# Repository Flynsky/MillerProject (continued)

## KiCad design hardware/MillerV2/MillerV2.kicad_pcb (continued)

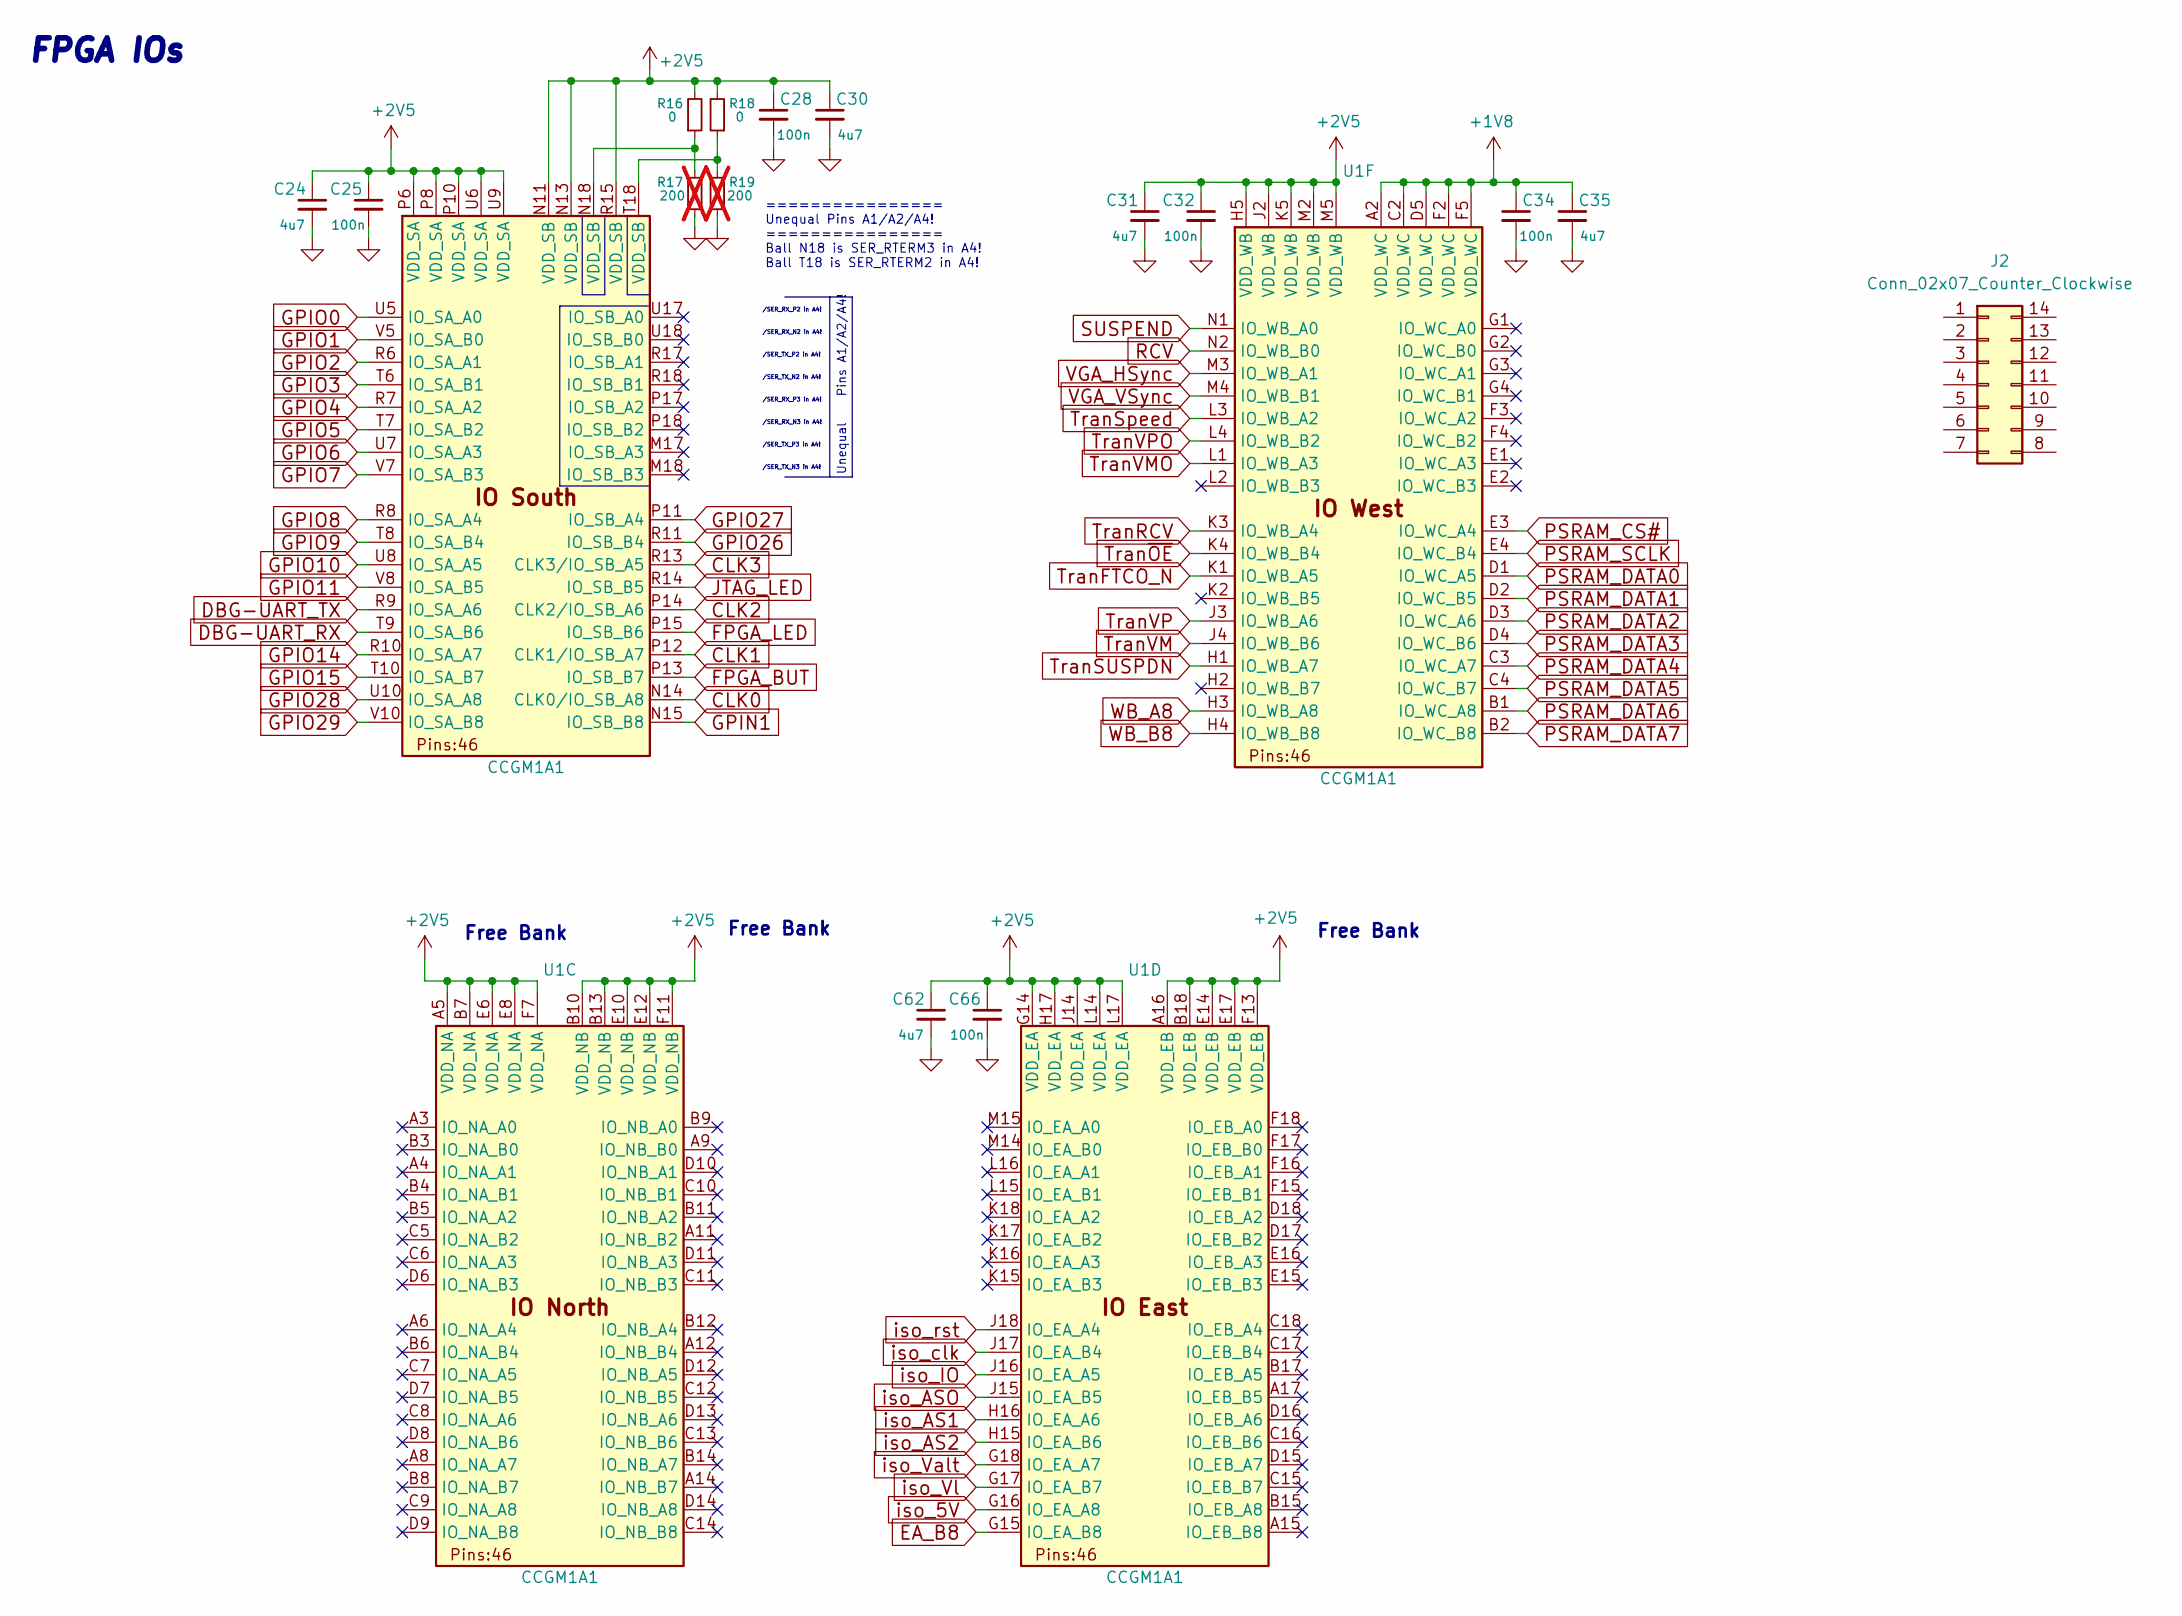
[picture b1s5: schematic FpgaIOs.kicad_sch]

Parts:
C24, C30, C31, C35, C62: 4u7; C_0402_1005Metric
C25, C28, C32, C34, C66: 100n; C_0402_1005Metric
J2: Conn_02x07_Counter_Clockwise; PinSocket_2x07_P2.54mm_Vertical_SMD
R16, R18: 0; R_0402_1005Metric
R17, R19: 200; R_0402_1005Metric; not fitted
U1: CCGM1A1; BGA-324_15x15mm_Layout18x18_P0.8mm_improvedUrsprung

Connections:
+1V8: C34.1, C35.1, U1.A2 (VDD_WC), U1.C2 (VDD_WC), U1.D5 (VDD_WC), U1.F2 (VDD_WC), U1.F5 (VDD_WC); also elsewhere on the board
+2V5: C24.1, C25.1, C28.1, C30.1, C31.1, C32.1, C62.1, C66.1, R16.2, R18.2, U1.A5 (VDD_NA), U1.A16 (VDD_EB), U1.B7 (VDD_NA), U1.B10 (VDD_NB), U1.B13 (VDD_NB), U1.B18 (VDD_EB), U1.E6 (VDD_NA), U1.E8 (VDD_NA), U1.E10 (VDD_NB), U1.E12 (VDD_NB), U1.E14 (VDD_EB), U1.E17 (VDD_EB), U1.F7 (VDD_NA), U1.F11 (VDD_NB), U1.F13 (VDD_EB), U1.G14 (VDD_EA), U1.H5 (VDD_WB), U1.H17 (VDD_EA), U1.J2 (VDD_WB), U1.J14 (VDD_EA), U1.K5 (VDD_WB), U1.L14 (VDD_EA), U1.L17 (VDD_EA), U1.M2 (VDD_WB), U1.M5 (VDD_WB), U1.N11 (VDD_SB), U1.N13 (VDD_SB), U1.P6 (VDD_SA), U1.P8 (VDD_SA), U1.P10 (VDD_SA), U1.R15 (VDD_SB), U1.U6 (VDD_SA), U1.U9 (VDD_SA); also elsewhere on the board
CLK0: U1.N14 (CLK0/IO_SB_A8); also elsewhere on the board
CLK1: U1.P12 (CLK1/IO_SB_A7); also elsewhere on the board
CLK2: U1.P14 (CLK2/IO_SB_A6); also elsewhere on the board
CLK3: U1.R13 (CLK3/IO_SB_A5); also elsewhere on the board
DBG-UART_RX: U1.T9 (IO_SA_B6); also elsewhere on the board
DBG-UART_TX: U1.R9 (IO_SA_A6); also elsewhere on the board
EA_B8: U1.G15 (IO_EA_B8); also elsewhere on the board
FPGA_BUT: U1.P13 (IO_SB_B7); also elsewhere on the board
FPGA_LED: U1.P15 (IO_SB_B6); also elsewhere on the board
GND: C24.2, C25.2, C28.2, C30.2, C31.2, C32.2, C34.2, C35.2, C62.2, C66.2, R17.1, R19.1; also elsewhere on the board
GPIN1: U1.N15 (IO_SB_B8); also elsewhere on the board
GPIO0: U1.U5 (IO_SA_A0); also elsewhere on the board
GPIO1: U1.V5 (IO_SA_B0); also elsewhere on the board
GPIO2: U1.R6 (IO_SA_A1); also elsewhere on the board
GPIO3: U1.T6 (IO_SA_B1); also elsewhere on the board
GPIO4: U1.R7 (IO_SA_A2); also elsewhere on the board
GPIO5: U1.T7 (IO_SA_B2); also elsewhere on the board
GPIO6: U1.U7 (IO_SA_A3); also elsewhere on the board
GPIO7: U1.V7 (IO_SA_B3); also elsewhere on the board
GPIO8: U1.R8 (IO_SA_A4); also elsewhere on the board
GPIO9: U1.T8 (IO_SA_B4); also elsewhere on the board
GPIO10: U1.U8 (IO_SA_A5); also elsewhere on the board
GPIO11: U1.V8 (IO_SA_B5); also elsewhere on the board
GPIO14: U1.R10 (IO_SA_A7); also elsewhere on the board
GPIO15: U1.T10 (IO_SA_B7); also elsewhere on the board
GPIO26: U1.R11 (IO_SB_B4); also elsewhere on the board
GPIO27: U1.P11 (IO_SB_A4); also elsewhere on the board
GPIO28: U1.U10 (IO_SA_A8); also elsewhere on the board
GPIO29: U1.V10 (IO_SA_B8); also elsewhere on the board
JTAG_LED: U1.R14 (IO_SB_B5); also elsewhere on the board
unnamed: R16.1, R17.2, U1.N18 (VDD_SB)
unnamed: R18.1, R19.2, U1.T18 (VDD_SB)
PSRAM_CS#: U1.E3 (IO_WC_A4); also elsewhere on the board
PSRAM_DATA0: U1.D1 (IO_WC_A5); also elsewhere on the board
PSRAM_DATA1: U1.D2 (IO_WC_B5); also elsewhere on the board
PSRAM_DATA2: U1.D3 (IO_WC_A6); also elsewhere on the board
PSRAM_DATA3: U1.D4 (IO_WC_B6); also elsewhere on the board
PSRAM_DATA4: U1.C3 (IO_WC_A7); also elsewhere on the board
PSRAM_DATA5: U1.C4 (IO_WC_B7); also elsewhere on the board
PSRAM_DATA6: U1.B1 (IO_WC_A8); also elsewhere on the board
PSRAM_DATA7: U1.B2 (IO_WC_B8); also elsewhere on the board
PSRAM_SCLK: U1.E4 (IO_WC_B4); also elsewhere on the board
RCV: U1.N2 (IO_WB_B0)
SUSPEND: U1.N1 (IO_WB_A0)
TranFTCO_N: U1.K1 (IO_WB_A5); also elsewhere on the board
TranRCV: U1.K3 (IO_WB_A4); also elsewhere on the board
TranSUSPDN: U1.H1 (IO_WB_A7); also elsewhere on the board
TranSpeed: U1.L3 (IO_WB_A2); also elsewhere on the board
TranVM: U1.J4 (IO_WB_B6); also elsewhere on the board
TranVMO: U1.L1 (IO_WB_A3); also elsewhere on the board
TranVP: U1.J3 (IO_WB_A6); also elsewhere on the board
TranVPO: U1.L4 (IO_WB_B2); also elsewhere on the board
Tran~OE: U1.K4 (IO_WB_B4); also elsewhere on the board
VGA_HSync: U1.M3 (IO_WB_A1)
VGA_VSync: U1.M4 (IO_WB_B1)
WB_A8: U1.H3 (IO_WB_A8); also elsewhere on the board
WB_B8: U1.H4 (IO_WB_B8); also elsewhere on the board
iso_5V: U1.G16 (IO_EA_A8); also elsewhere on the board
iso_AS1: U1.H16 (IO_EA_A6); also elsewhere on the board
iso_AS2: U1.H15 (IO_EA_B6); also elsewhere on the board
iso_ASO: U1.J15 (IO_EA_B5); also elsewhere on the board
iso_IO: U1.J16 (IO_EA_A5); also elsewhere on the board
iso_Valt: U1.G18 (IO_EA_A7); also elsewhere on the board
iso_Vl: U1.G17 (IO_EA_B7); also elsewhere on the board
iso_clk: U1.J17 (IO_EA_B4); also elsewhere on the board
iso_rst: U1.J18 (IO_EA_A4); also elsewhere on the board

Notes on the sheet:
/SER_TX_N2 in A4!
Free Bank
================ Unequal Pins A1/A2/A4! ================ Ball N18 is SER_RTERM3 in A4! Ball T18 is SER_RTERM2 in A4!
/SER_RX_N3 in A4!
/SER_TX_N3 in A4!
FPGA IOs
/SER_RX_P3 in A4!
/SER_TX_P2 in A4!
/SER_RX_N2 in A4!
/SER_RX_P2 in A4!
/SER_TX_P3 in A4!
Unequal Pins A1/A2/A4!

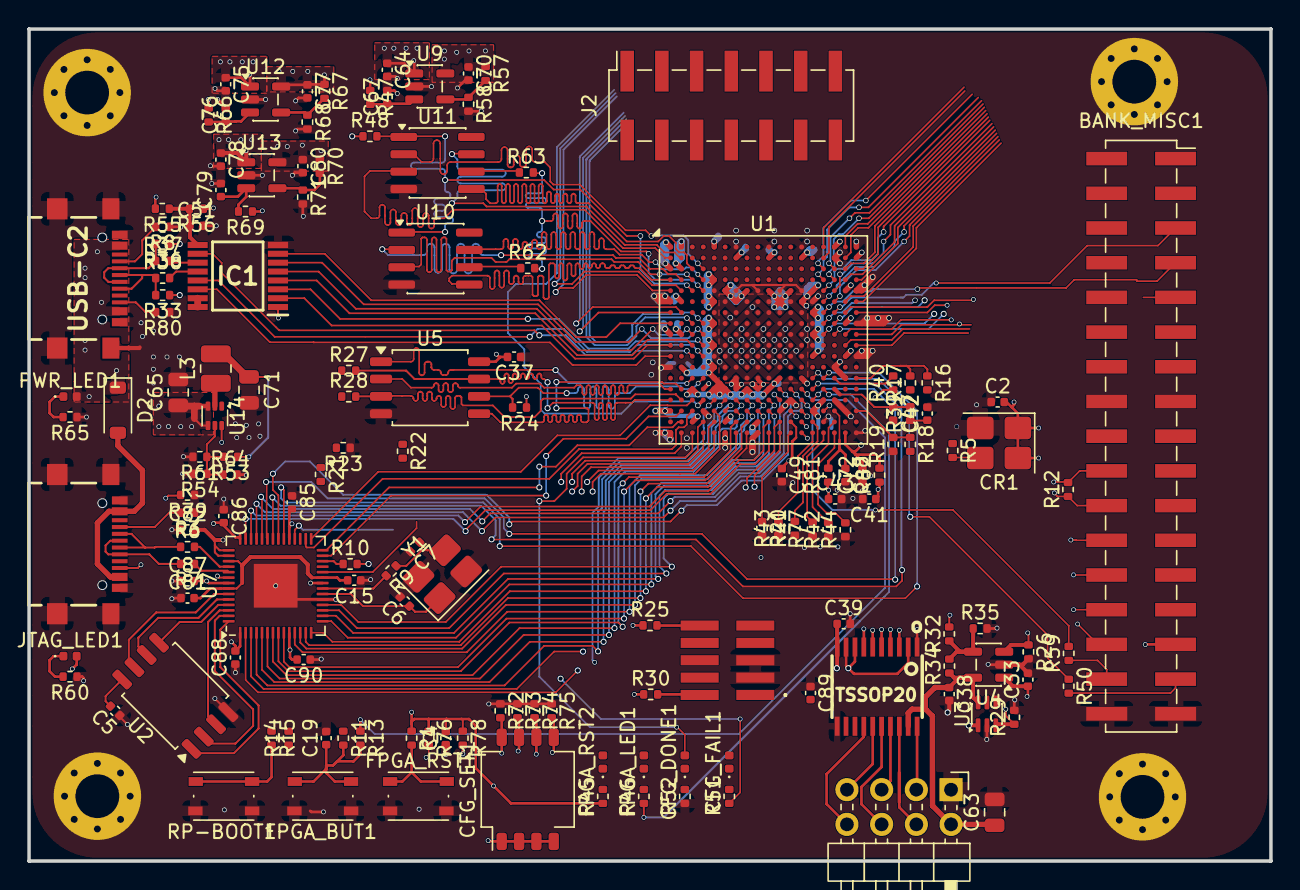
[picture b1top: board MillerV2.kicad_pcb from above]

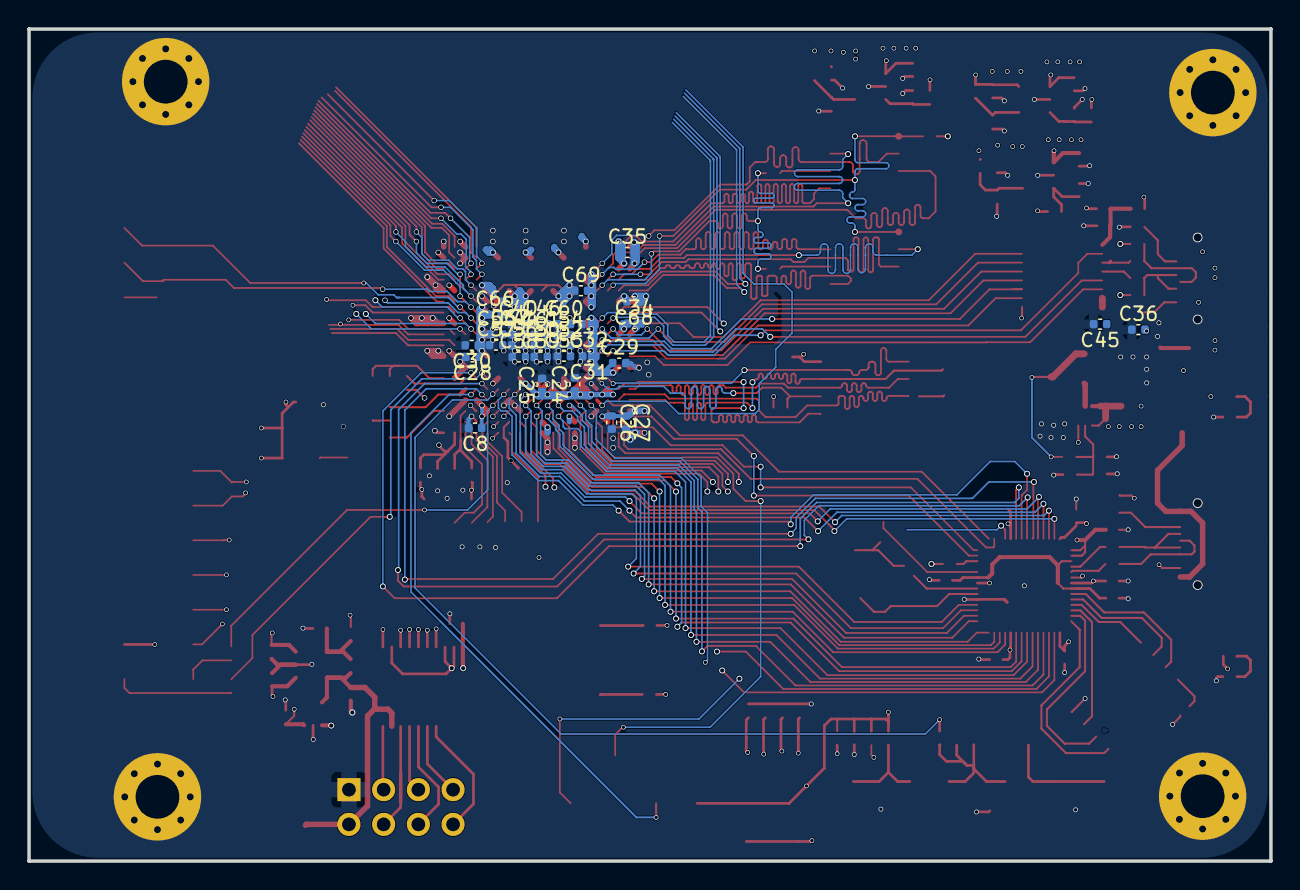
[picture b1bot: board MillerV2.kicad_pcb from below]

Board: 4 copper layers, 90.9 x 60.9 mm, 187 parts (32 on the bottom side), 160 nets.

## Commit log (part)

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2026-03-30 added Olimex hard and softare, reformed schemaktic to make human readable
2026-04-07 Added git ignore file
2026-04-07 sys_verilog_test folder with Makefile for some flash tests for the olimex board
2026-04-22 made room for tobi
2026-04-28 added VCC siwtcher for ISO Interface
2026-05-02 TUSB hinzugefügt muss aber noch gerouted werden
2026-05-02 KiCad Änderungen - Zwischenstand
2026-05-04 merged USB PHY
2026-05-04 added BOM and pinlist
2026-05-09 assigned FPGA pins to USB PHY
2026-05-12 added graphics
2026-05-12 added
2026-05-15 Updated BOM(now seperate Folder)
2026-05-17 Alles Kapput mach das neu in MAIN
2026-05-17 History in gitignore
2026-05-17 kleine Änderungen und GND
2026-05-18 fixed scematic/pcb differences
2026-05-21 Update PCB footprints and USB power nets
    Modify MillerV1.kicad_pcb: fix USB power net assignments and clean up footprints. Several USB VBUS pads were retargeted from +5V_USB (and +5V_USB_2) to the correct nets (Net-(D3-A) or +5V_USB). Added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
2026-05-22 sollte soweit fertig sein
2026-05-22 solved some DRC issues
2026-05-22 solved some DRC issues, downgraded from nightly to standard kicad yeay
2026-06-01 minor changes
